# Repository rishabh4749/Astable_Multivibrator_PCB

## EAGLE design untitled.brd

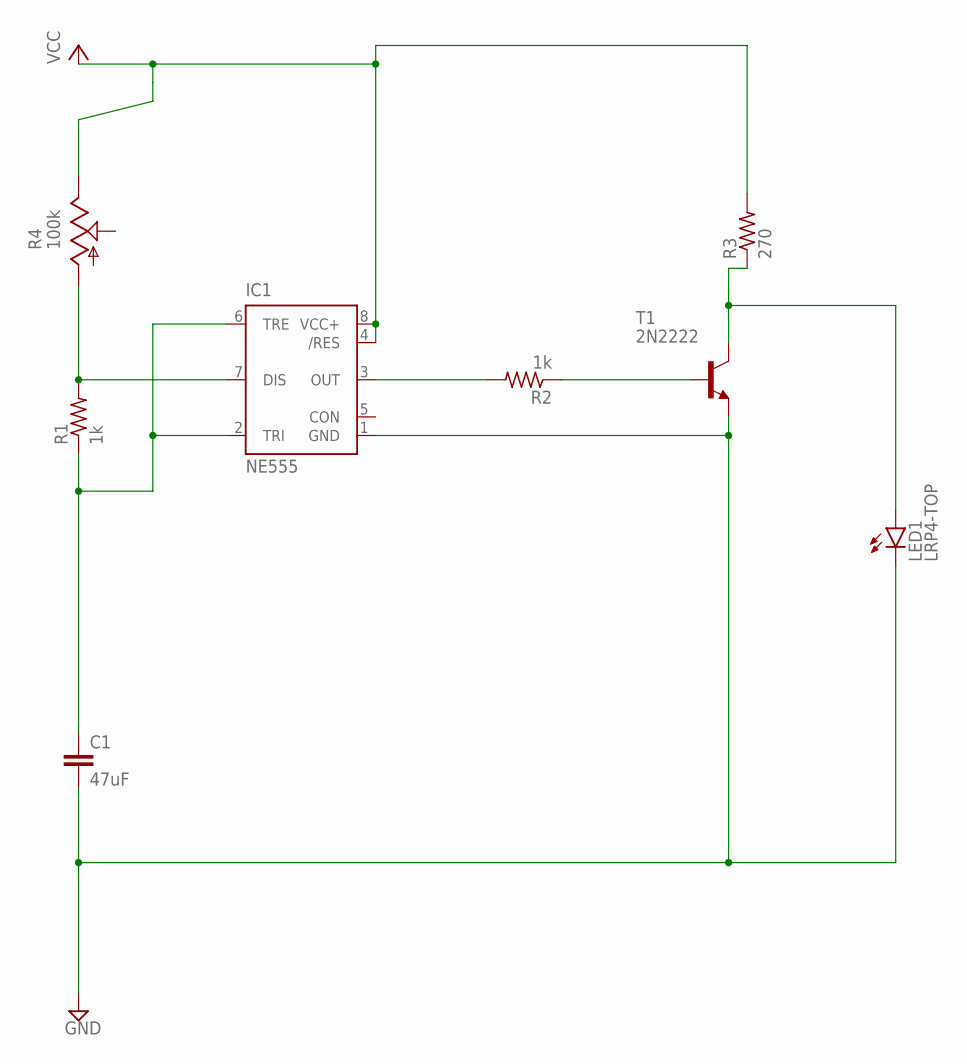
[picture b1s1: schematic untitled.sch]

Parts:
C1: 47uF; C050-035X075
IC1: NE555; DIL-08
LED1: LRP4-TOP; P47F-TOP
R1, R2: 1k; 0204/5
R3: 270; 0204/5
R4: 100k; RJ6S
T1: 2N2222; TO18

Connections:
GND: C1.2, IC1.1 (GND), LED1.C, T1.1 (E)
unnamed: IC1.7 (DIS), R1.2, R4.A
unnamed: IC1.3 (OUT), R2.2
unnamed: R2.1, T1.2 (B)
unnamed: LED1.A, R3.1, T1.3 (C)
unnamed: C1.1, IC1.2 (TRI), IC1.6 (TRE), R1.1
VCC: IC1.4 (/RES), IC1.8 (VCC+), R3.2, R4.E

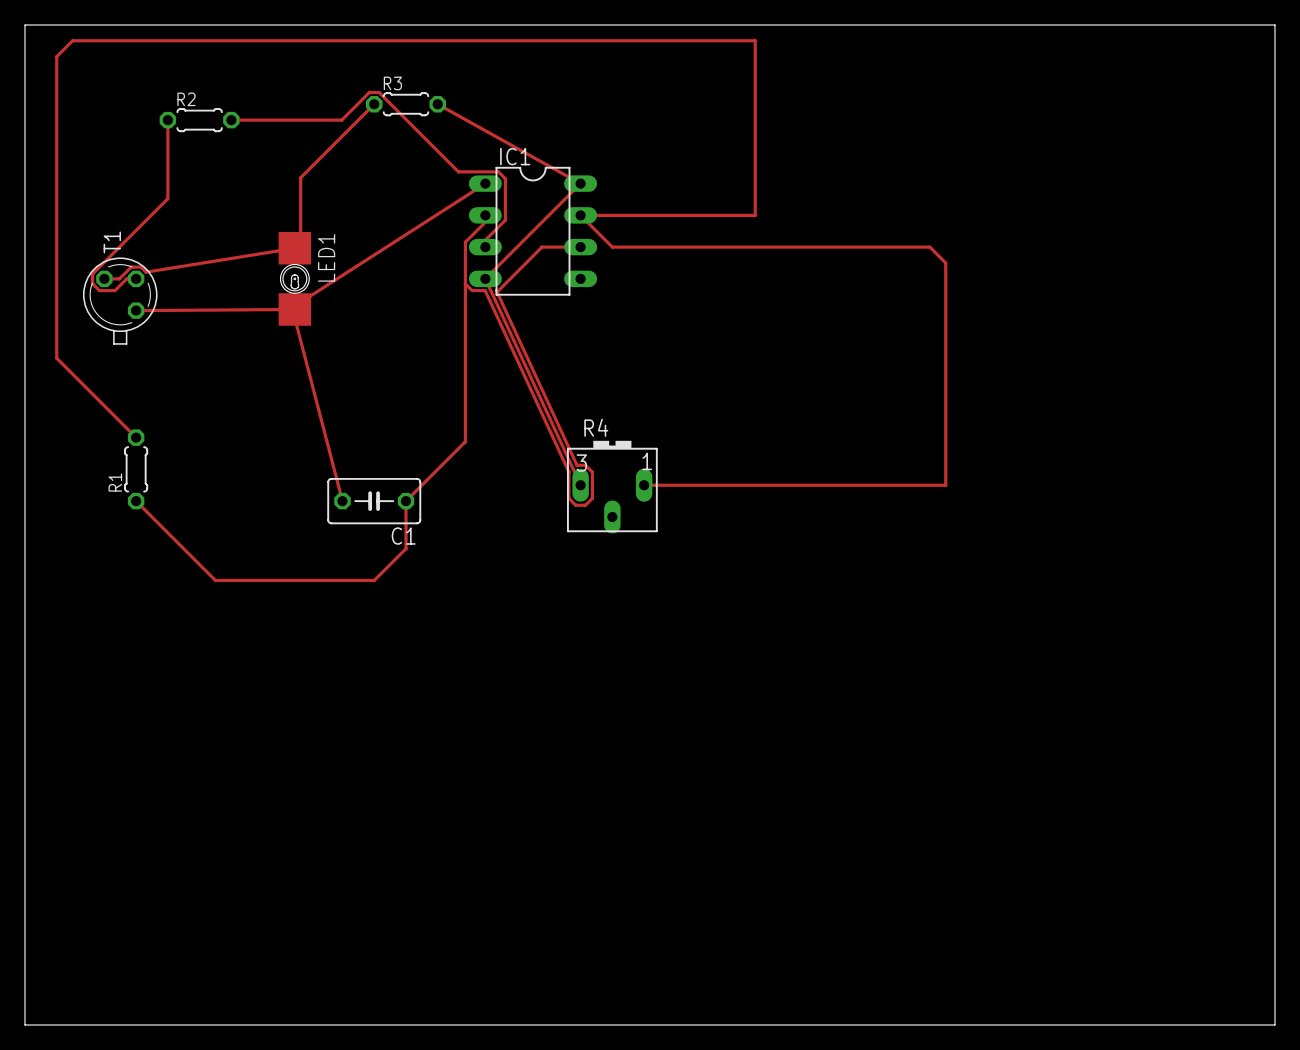
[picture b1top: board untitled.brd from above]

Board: 2 copper layers, 100.0 x 80.0 mm, 8 parts (0 on the bottom side), 7 nets.
